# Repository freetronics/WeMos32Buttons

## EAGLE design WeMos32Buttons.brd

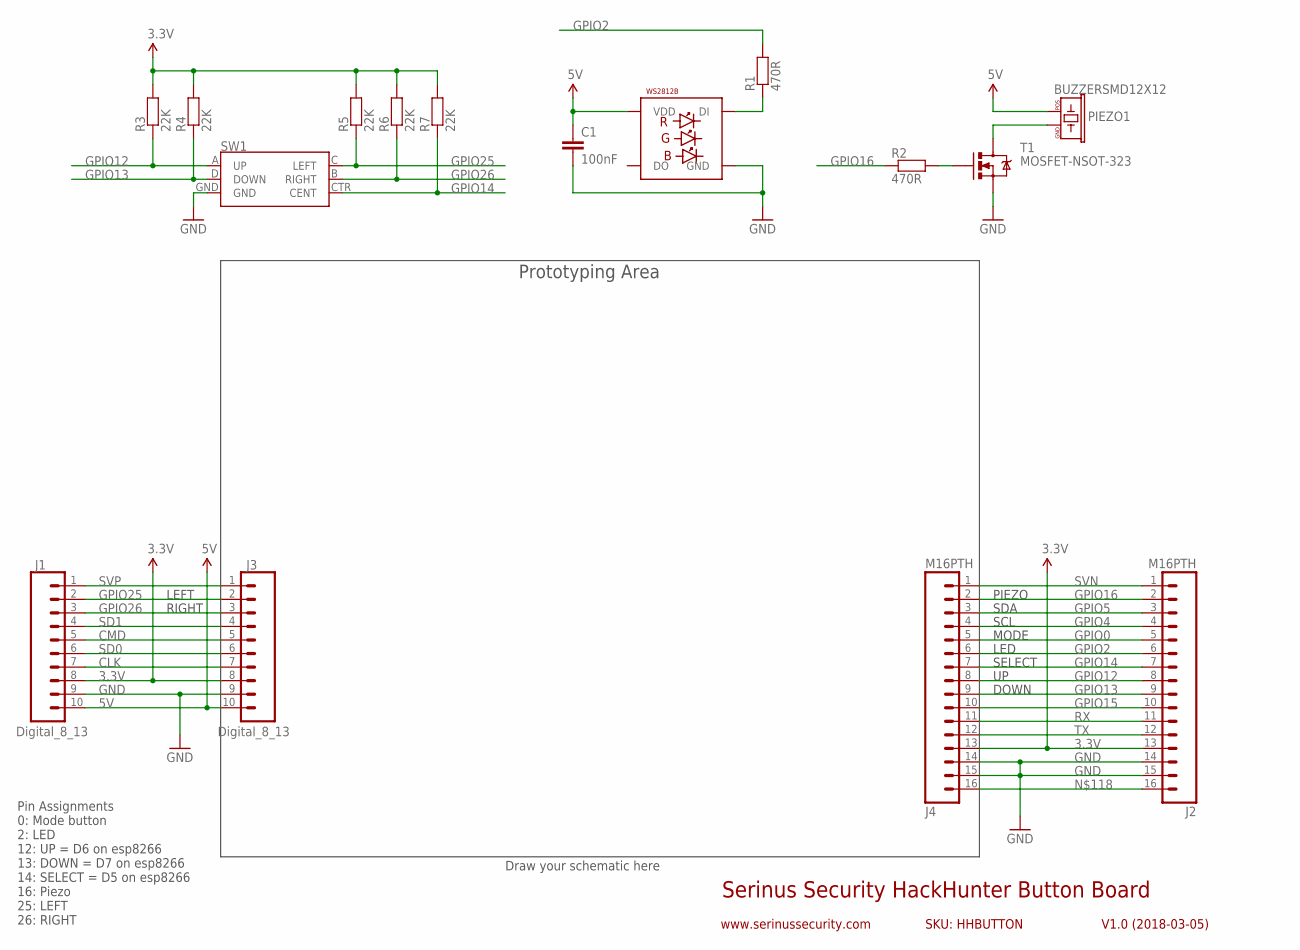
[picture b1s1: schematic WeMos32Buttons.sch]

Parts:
C1: 100nF; 0603
J1, J3: Digital_8_13; 1X10
J2, J4: M16PTH; 1X16
LED2: WS2812B5050; WS2812B
PIEZO1: BUZZERSMD12X12; BUZZER-12X12-SMT
R1, R2: 470R; 0603
R3, R4, R5, R6, R7: 22K; 0603
SW1: JOYSTICK_MINI
T1: MOSFET-NSOT-323; SOT32-3

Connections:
3.3V: J1.8, J2.13, J3.8, J4.13, R3.2, R4.2, R5.2, R6.2, R7.2
5V: C1.1, J1.10, J3.10, LED2.1-VDD (VDD), PIEZO1.2 (POS)
CLK: J1.7, J3.7
CMD: J1.5, J3.5
GND: C1.2, J1.9, J2.14, J2.15, J3.9, J4.14, J4.15, LED2.3-GND (GND), SW1.GND, T1.2 (S)
GPIO0: J2.5, J4.5
GPIO2: J2.6, J4.6, R1.2
GPIO4: J2.4, J4.4
GPIO5: J2.3, J4.3
GPIO12: J2.8, J4.8, R3.1, SW1.A (UP)
GPIO13: J2.9, J4.9, R4.1, SW1.D (DOWN)
GPIO14: J2.7, J4.7, R7.1, SW1.CTR (CENT)
GPIO15: J2.10, J4.10
GPIO16: J2.2, J4.2, R2.1
GPIO25: J1.2, J3.2, R5.1, SW1.C (LEFT)
GPIO26: J1.3, J3.3, R6.1, SW1.B (RIGHT)
unnamed: PIEZO1.1 (GND), T1.3 (D)
unnamed: R2.2, T1.1 (G)
unnamed: J2.16, J4.16
unnamed: LED2.4-DIN (DI), R1.1
RX: J2.11, J4.11
SD0: J1.6, J3.6
SD1: J1.4, J3.4
SVN: J2.1, J4.1
SVP: J1.1, J3.1
TX: J2.12, J4.12

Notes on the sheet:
Serinus Security HackHunter Button Board
V1.0 (2018-03-05)
www.serinussecurity.com
SKU: HHBUTTON
Pin Assignments 0: Mode button 2: LED 12: UP = D6 on esp8266 13: DOWN = D7 on esp8266 14: SELECT = D5 on esp8266 16: Piezo 25: LEFT 26: RIGHT
Draw your schematic here
Prototyping Area
LED
DOWN
SELECT
MODE
SDA
SCL
PIEZO
LEFT
RIGHT

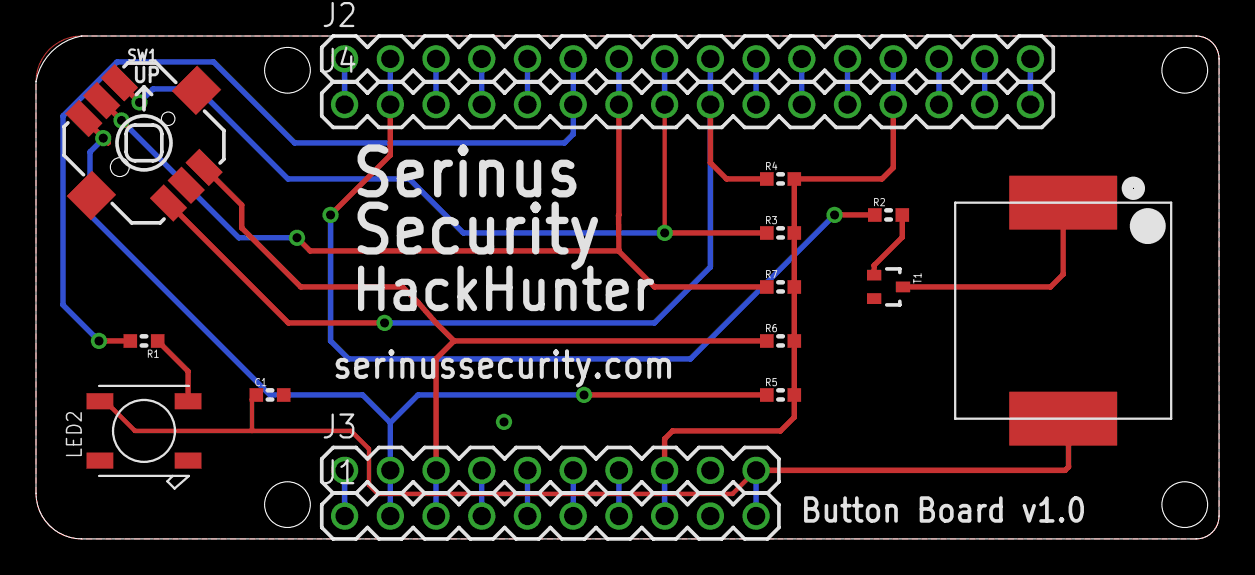
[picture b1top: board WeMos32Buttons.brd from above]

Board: 2 copper layers, 65.7 x 27.9 mm, 16 parts (0 on the bottom side), 26 nets.

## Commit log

2018-03-09 Initial project import
2018-03-19 Added pull-ups on all inputs, restructured to fit fake WeMos board
2019-04-24 Removed branding

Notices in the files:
WeMos32Buttons.brd:
(C)2018 Serinus Security Pty Ltd
All Rights Reserved
parts and their libraries:
SparkFun-Switches: Licensing: Creative Commons ShareAlike 4.0 International - https://creativecommons.org/licenses/by-sa/4.0
